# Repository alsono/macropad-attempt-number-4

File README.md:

# Introduction 
this is my first ever macropad! (or at least the 1st one i'll actually ship). <br/>
you can tell i'm not very good at cad lmao <br/>
check the bom (bill of materials) for all you'll need (excluding the case and pcb of course)
## what is a macropad?
its like a little keyboard that you get to build and program yourself! this one per example is made to help me to copy, paste, undo and redo! <br/>
of course you can change what the buttons do and even display stuff on the screen if you know qmk (the oled currently shows nothing i'll make it display stuff based on what button you press in the next devlog)
## images of the whole project
case (3d printable you'll find the lid and main thing seperated in the production folder)
<br/>

schematic and pcb designs made using kicad you can order the pcb from jlcpcb using the gerber zip file in the productions folder

and now for the whole thing soldered and assembled (if you don't know how to solder it/can't tell what's where from the images open the .step file using onshape or any cad software and remove the case to see how its supposed to look!)

# for any further questions if you want to make this yourself hit me up on slack, name's @The Blue Reverberation

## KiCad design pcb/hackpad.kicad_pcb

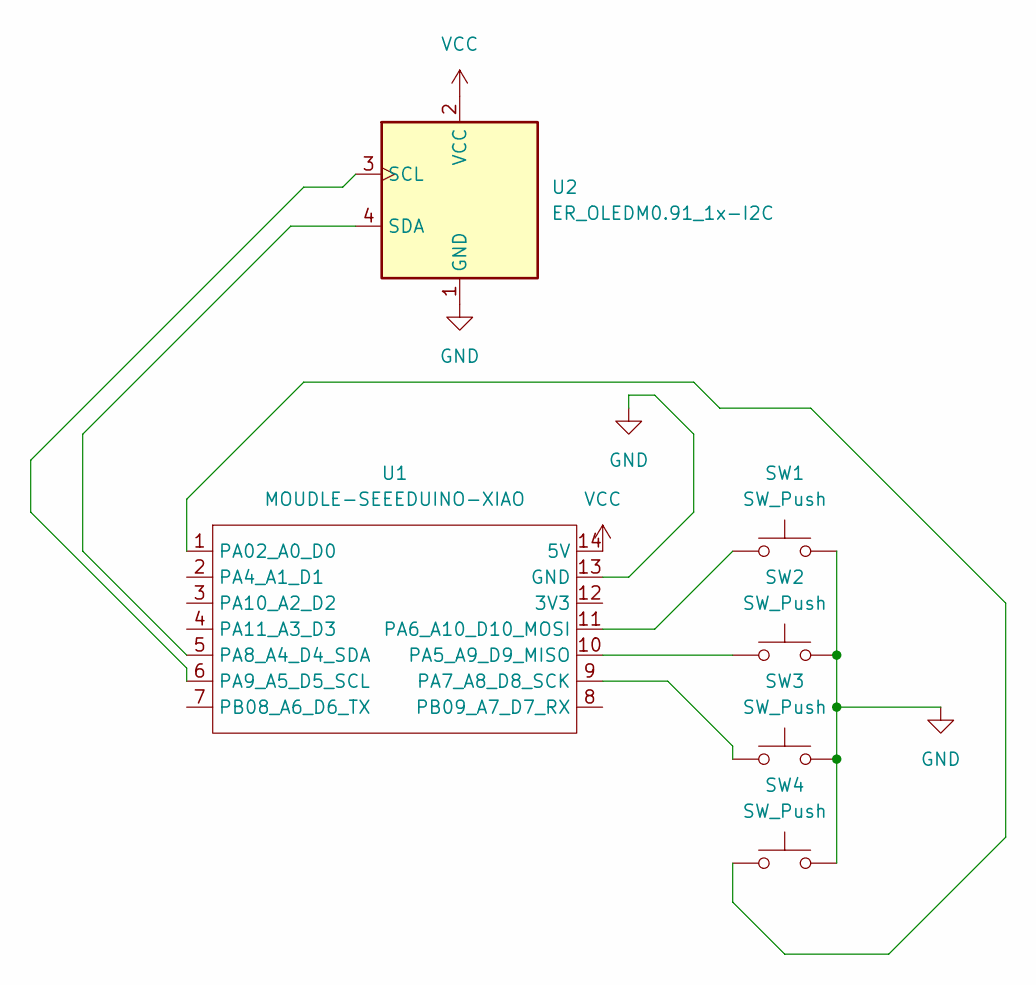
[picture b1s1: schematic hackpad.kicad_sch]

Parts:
SW1, SW2, SW3, SW4: SW_Push; SW_Cherry_MX_1.00u_PCB
U1: MOUDLE-SEEEDUINO-XIAO; XIAO-Generic-Hybrid-14P-2.54-21X17.8MM
U2: ER_OLEDM0.91_1x-I2C

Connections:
GND: SW1.2, SW2.2, SW3.2, SW4.2, U1.13 (GND), U2.1 (GND)
unnamed: SW4.1, U1.1 (PA02_A0_D0)
unnamed: SW2.1, U1.10 (PA5_A9_D9_MISO)
unnamed: SW1.1, U1.11 (PA6_A10_D10_MOSI)
unnamed: SW3.1, U1.9 (PA7_A8_D8_SCK)
unnamed: U1.5 (PA8_A4_D4_SDA), U2.4 (SDA)
unnamed: U1.6 (PA9_A5_D5_SCL), U2.3 (SCL)
VCC: U1.14 (5V), U2.2 (VCC)

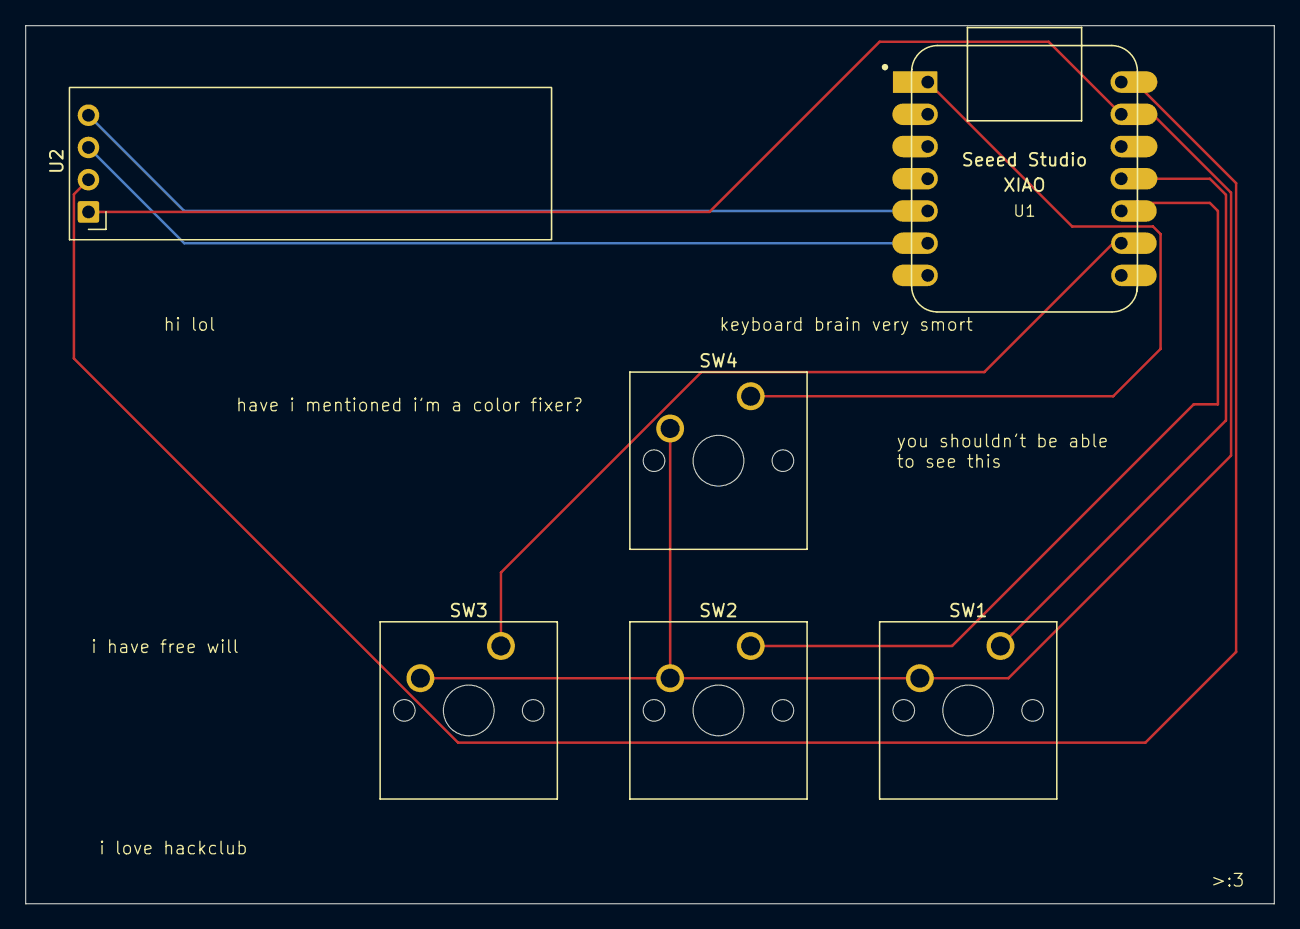
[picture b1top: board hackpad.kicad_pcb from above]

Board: 2 copper layers, 98.4 x 69.2 mm, 6 parts (0 on the bottom side), 8 nets.
